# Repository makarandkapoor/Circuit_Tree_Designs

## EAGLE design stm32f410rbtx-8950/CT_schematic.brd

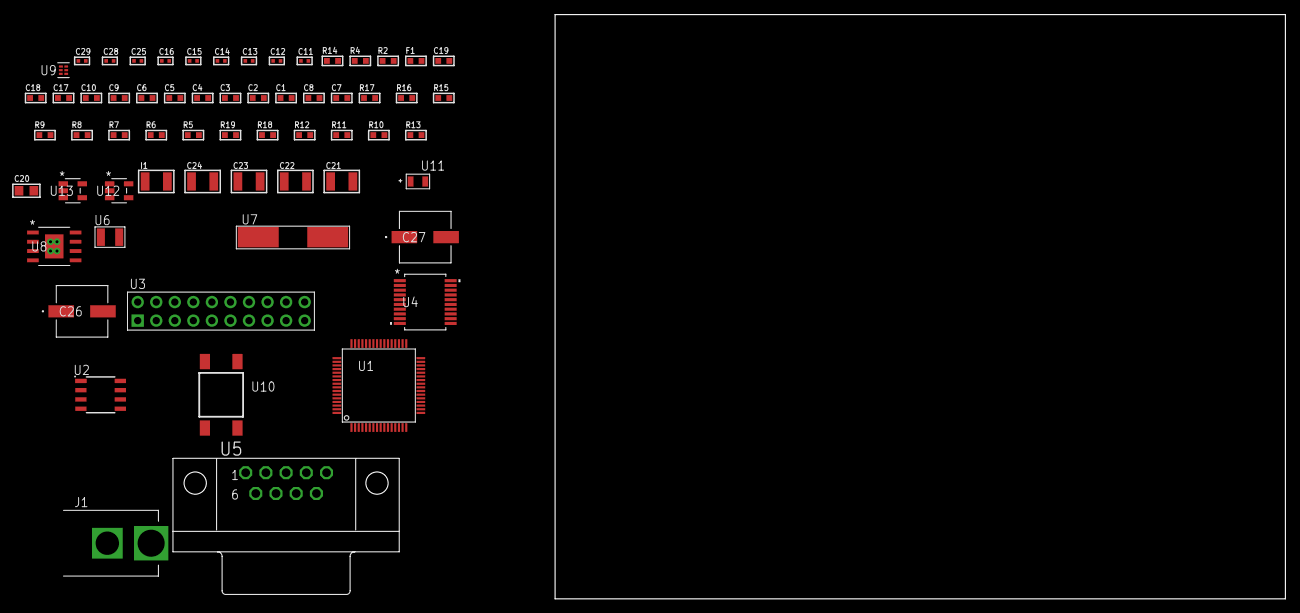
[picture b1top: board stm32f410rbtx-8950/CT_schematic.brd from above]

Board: 2 copper layers, 100.0 x 80.0 mm, 62 parts (0 on the bottom side), 43 nets, no tracks yet.

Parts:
C1, C10, C17, C18, C19: 1e-06; C0603
C2, C3, C4, C5, C6: 1e-07; C0603
C7: 4.7e-06; C0603
C8: 2.2e-06; C0603
C9: 1e-08; C0603
C11, C12, C13, C14: 1e-11; C0402
C15, C28, C29: 1e-08; C0402
C16, C25: 1e-07; C0402
C20: 4.7e-06; C0805
C21, C22, C23, C24: 1e-05; C1210
C26, C27: 0.0001; EXV-9H
F1: 240.0; L0603
I1: 1.5e-05; L1210
J1: PJ-037B; PJ-037B_PACKAGE
R2: 1000.0; R0603
R4: 4700.0; R0603
R5, R6, R7, R8, R9, R15, R16: 10000.0; R0603
R10, R11, R12: 100000.0; R0603
R13: 1402.2764227642; R0603
R14: 2200.0; R0603
R17: 82000.0; R0603
R18: 300000.0; R0603
R19: 120000.0; R0603
U1: STM32F410RBT6; LQFP64
U2: AT25128B-SSHL-T; SOIC-8
U3: TST-110-05-T-D-RA
U4: MAX3218EAP+T; SSOP-20
U5: 182-009-113R531; 182-009-MALE
U6: ABS07-32.768KHZ-7-T
U7: ABLS-25.000MHZ-B2F-T
U8: MIC5234YME; SOIC-8_EP
U9: TPS3895ADRYR; SON-6
U10: 4-1437565-2; SW_4-1437565-2
U11: Q65110A2395; LGM67K-G1J2-24-Z
U12, U13: nc7sz125m5x; NC7SZ125M5X

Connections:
CLK_CRYSTAL_U1_3: C11.1, U1.3, U6.1
CLK_CRYSTAL_U1_4: C12.1, U1.4, U6.2
CLK_CRYSTAL_U1_5: C13.1, U1.5, U7.1
CLK_CRYSTAL_U1_6: C14.1, U1.6, U7.2
GND: C1.2, C2.2, C3.2, C4.2, C5.2, C6.2, C7.2, C8.2, C9.2, C10.2, C11.2, C12.2, C13.2, C14.2, C15.2, C16.2, C17.2, C18.2, C19.2, C21.2, C22.2, C23.2, C24.2, C25.2, C26.2, C27.2, C28.2, C29.2, J1.2, R2.2, R5.2, R14.2, R17.2, R19.2, U1.12, U1.18, U1.31, U1.47, U1.63, U2.4, U3.4, U3.6, U3.8, U3.10, U3.12, U3.14, U3.16, U3.18, U3.20, U4.5, U4.17, U4.20, U5.5, U8.7, U8.EPAD, U9.2, U11.C, U12.2, U12.3, U13.1, U13.3
NET_U1_7: R4.1, U1.7, U13.4
NET_U1_13: C9.1, C10.1, F1.1, U1.13
NET_U1_30: C8.1, U1.30
NET_U1_60: R5.1, U1.60
NET_U1_62: U10.3, U10.4
NET_U2_3: R6.1, U2.3
NET_U2_7: R8.1, U2.7
NET_U4_1: I1.1, U4.1
NET_U4_2: R10.1, U4.2
NET_U4_3: R11.1, U4.3
NET_U4_4: R12.1, U4.4
NET_U4_15: C19.1, U4.15
NET_U4_16: C20.2, U4.16
NET_U4_18: C20.1, U4.18
NET_U4_19: C18.1, U4.19
NET_U5_2: U4.12, U5.2
NET_U5_3: U4.14, U5.3
NET_U5_7: U4.11, U5.7
NET_U5_8: U4.13, U5.8
NET_U8_4: R13.2, R14.1, U8.4
NET_U9_1: R16.1, R17.1, U9.1
NET_U9_3: R18.2, R19.1, U9.3
NET_U9_4: R15.1, U9.4, U12.4, U13.2
NET_U10_1: R2.1, U10.1, U10.2
PROC_SPI1_MISO: U1.22, U2.2
PROC_SPI1_MOSI: U1.23, U2.5
PROC_SPI1_NSS: R7.1, U1.20, U2.1
PROC_SPI1_SCK: U1.21, U2.6
PROC_SYS_JTCK_SWCLK: U1.49, U3.9
PROC_SYS_JTDO_SWO: U1.55, U3.13
PROC_SYS_JTMS_SWDIO: U1.46, U3.7
PROC_USART1_CTS: U1.44, U4.8
PROC_USART1_RTS: U1.45, U4.10
PROC_USART1_RX: U1.43, U4.9
PROC_USART1_TX: U1.42, U4.7
RST_OUT_U3_SRESET_B: R9.1, U3.15, U12.1
VCC_S1_9V9: C21.1, C22.1, C26.1, C27.1, J1.1, U8.5, U8.8
VCC_TIER1_1V8: C1.1, C2.1, C3.1, C4.1, C5.1, C6.1, C7.1, C15.1, C16.1, C17.1, C23.1, C24.1, C25.1, C28.1, C29.1, F1.2, I1.2, R4.2, R6.2, R7.2, R8.2, R9.2, R10.2, R11.2, R12.2, R13.1, R15.2, R16.2, R18.1, U1.1, U1.19, U1.32, U1.48, U1.64, U2.8, U3.1, U4.6, U8.1, U9.6, U12.5, U13.5

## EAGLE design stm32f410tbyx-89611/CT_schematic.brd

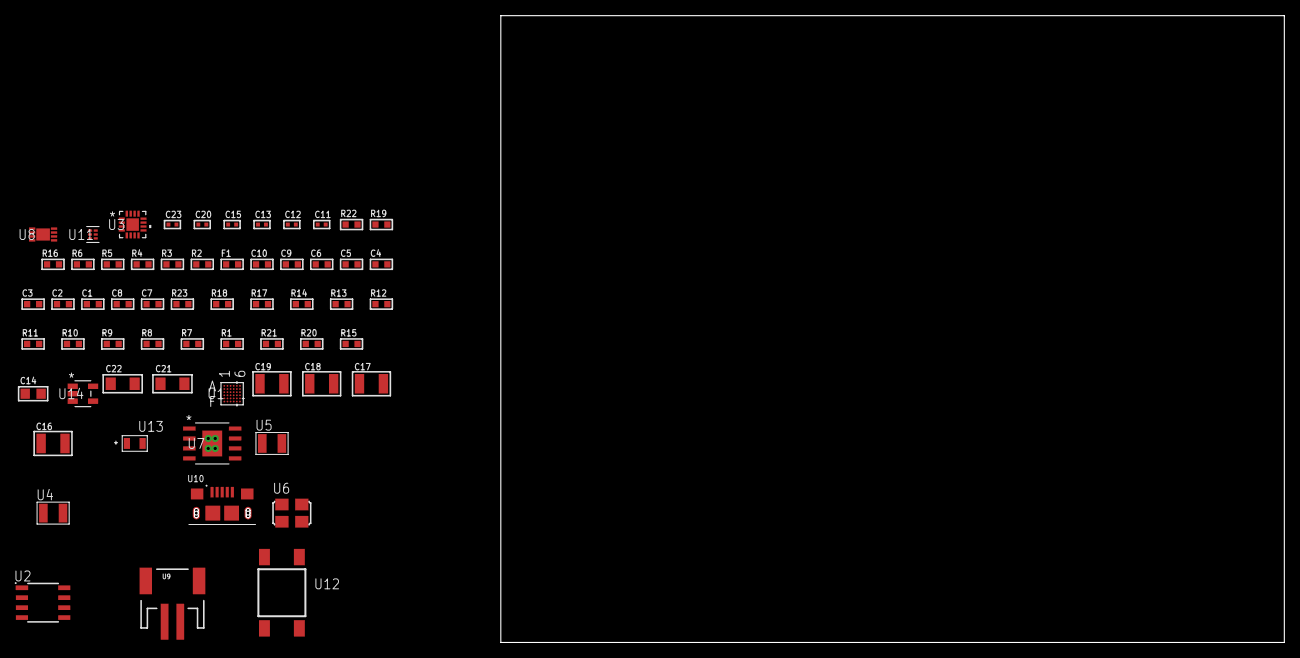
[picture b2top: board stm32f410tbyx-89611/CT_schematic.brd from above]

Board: 2 copper layers, 61 parts (0 on the bottom side), 33 nets, no tracks yet.

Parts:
C1, C10: 1e-06; C0603
C2, C3, C4, C5, C6: 1e-07; C0603
C7: 4.7e-06; C0603
C8: 2.2e-06; C0603
C9: 1e-08; C0603
C11, C12: 1e-11; C0402
C13, C15, C23: 1e-08; C0402
C14: 4.7e-06; C0805
C16, C17, C18, C19: 1e-05; C1210
C20: 1e-07; C0402
C21, C22: 1e-05; C1206
F1: 240.0; L0603
R1, R7, R8, R9, R10, R11, R12, R13, R14, R17, R18, R23: 10000.0; R0603
R2: 1000.0; R0603
R3: 1600.5; R0603
R4: 4700.0; R0603
R5, R6, R16: 2200.0; R0603
R15: 4031.5447154472; R0603
R19: 9100.0; R0603
R20: 680000.0; R0603
R21: 120000.0; R0603
R22: 2000.0; R0603
U1: STM32F410TBY6; WLCSP36
U2: AT25640B-SSHL-T; SOIC-8
U3: M41T65Q6F; M41T65_QFN-16
U4, U5: ABS07-32.768KHZ-7-T
U6: ASFL1-25MHZ-NCS; ASFL1
U7: MIC5234YME; SOIC-8_EP
U8: MCP73831T-2ACI/MC; DFN8_2X3MC
U9: S2B-PH-SM4-TB(LF)(SN); JST-2-SMD
U10: 10118193-0001LF; FCI_10118193-0001LF
U11: TPS3895ADRYR; SON-6
U12: 4-1437565-2; SW_4-1437565-2
U13: Q65110A2395; LGM67K-G1J2-24-Z
U14: nc7sz125m5x; NC7SZ125M5X

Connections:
CLK_CRYSTAL_U1_B6: C11.1, U1.B6, U5.1
CLK_CRYSTAL_U1_C6: C12.1, U1.C6, U5.2
CLK_CRYSTAL_U3_1: U3.1, U4.1
CLK_CRYSTAL_U3_2: U3.2, U4.2
CLK_U1_C5: U1.C5, U6.3
GND: C1.2, C2.2, C3.2, C4.2, C5.2, C6.2, C7.2, C8.2, C9.2, C10.2, C11.2, C12.2, C13.2, C14.2, C15.2, C16.2, C17.2, C18.2, C19.2, C20.2, C21.2, C22.2, C23.2, R2.2, R8.2, R16.2, R19.2, R21.2, R22.2, U1.A5, U1.B1, U1.E6, U1.F2, U2.4, U3.3, U3.5, U3.17, U6.2, U7.7, U7.EPAD, U8.6, U8.9, U9.2, U10.5, U10.6, U10.7, U10.8, U10.9, U11.2, U13.C, U14.1, U14.3
INPUT_USBPOWER_5V: C21.1, R23.2, U8.1, U8.2, U10.1
NET_U1_A4: R5.1, U1.A4, U3.10
NET_U1_B4: R7.1, R9.1, U1.B4
NET_U1_C3: R6.1, U1.C3, U3.9
NET_U1_D4: R8.1, U1.D4
NET_U1_D5: R4.1, U1.D5, U14.4
NET_U1_E2: C8.1, U1.E2
NET_U1_F4: R3.1, U1.F4, U13.A
NET_U1_F5: R1.1, U1.F5, U12.3, U12.4
NET_U1_F6: C9.1, C10.1, F1.1, U1.F6
NET_U2_3: R10.1, U2.3
NET_U2_7: R12.1, U2.7
NET_U3_4: R13.1, U3.4
NET_U3_11: R14.1, U3.11
NET_U7_4: R15.2, R16.1, U7.4
NET_U8_5: R23.1, U8.5
NET_U8_8: R22.1, U8.8
NET_U11_1: R18.1, R19.1, U11.1
NET_U11_3: R20.2, R21.1, U11.3
NET_U11_4: R17.1, U11.4, U14.2
NET_U12_1: R2.1, U12.1, U12.2
PROC_SPI1_MISO: U1.D3, U2.2
PROC_SPI1_MOSI: U1.A3, U2.5
PROC_SPI1_NSS: R11.1, U1.A2, U2.1
PROC_SPI1_SCK: U1.C2, U2.6
VCC_S1_3V7: C16.1, C17.1, C22.1, U7.5, U7.8, U8.3, U8.4, U9.1
VCC_TIER1_3V3: C1.1, C2.1, C3.1, C4.1, C5.1, C6.1, C7.1, C13.1, C14.1, C15.1, C18.1, C19.1, C20.1, C23.1, F1.2, R1.2, R3.2, R4.2, R5.2, R6.2, R7.2, R9.2, R10.2, R11.2, R12.2, R13.2, R14.2, R15.1, R17.2, R18.2, R20.1, U1.A1, U1.A6, U1.B5, U1.F1, U2.8, U3.14, U6.4, U7.1, U11.6, U14.5

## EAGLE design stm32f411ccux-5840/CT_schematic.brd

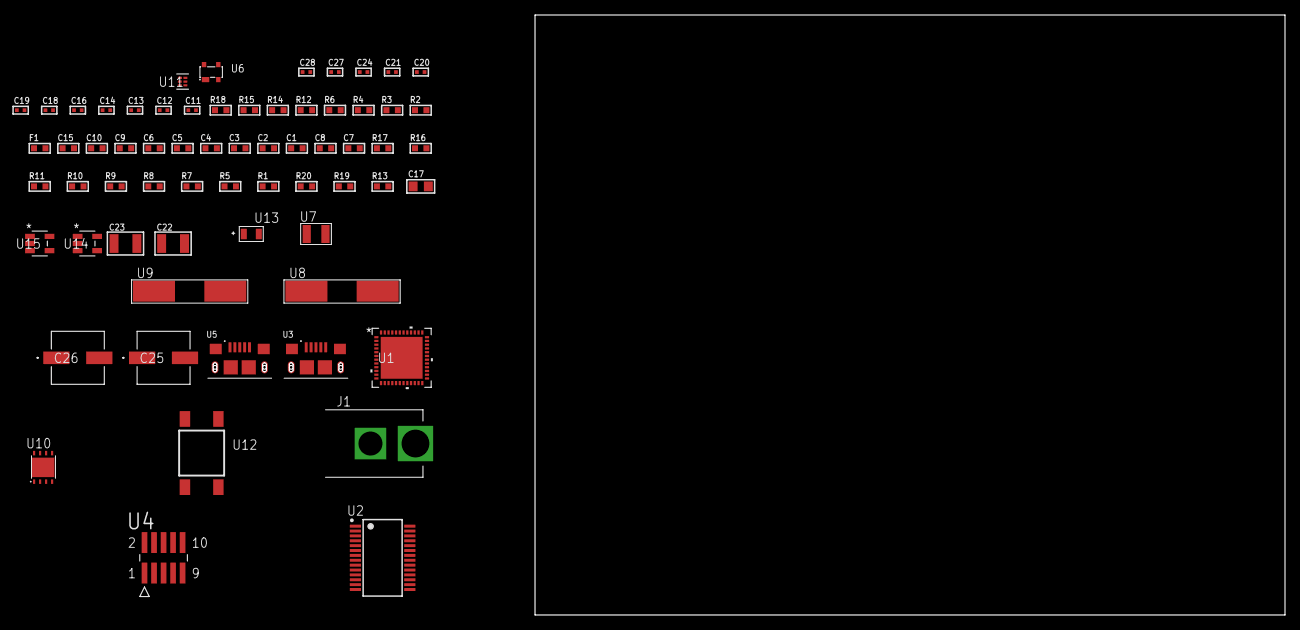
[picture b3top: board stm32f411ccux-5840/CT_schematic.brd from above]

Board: 2 copper layers, 65 parts (0 on the bottom side), 40 nets, no tracks yet.

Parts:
C1, C10, C15: 1e-06; C0603
C2, C3, C4, C5, C6: 1e-07; C0603
C7: 4.7e-06; C0603
C8: 2.2e-06; C0603
C9: 1e-08; C0603
C11, C12, C13, C14: 1e-11; C0402
C16, C18, C19, C20, C24: 1e-07; C0402
C17: 4.7e-06; C0805
C21, C27, C28: 1e-08; C0402
C22, C23: 1e-05; C1210
C25, C26: 0.0001; EXV-9H
F1: 240.0; L0603
J1: PJ-037B; PJ-037B_PACKAGE
R1, R5, R7, R8, R9, R10, R11, R16, R17: 10000.0; R0603
R2, R15: 1000.0; R0603
R3: 1600.5; R0603
R4, R6: 4700.0; R0603
R12: 5.0; R0603
R13: 100000.0; R0603
R14: 2231.0; R0603
R18: 9100.0; R0603
R19: 680000.0; R0603
R20: 120000.0; R0603
U1: STM32F411CCU6; UFQFPN48
U2: FT232RL-REEL; SSOP-28
U3, U5: 10118193-0001LF; FCI_10118193-0001LF
U4: FTSH-105-01-L-DV-K; SAMTEC_FTSH-105-01-L-DV-K
U6: prtr5v0u2ax; SOT143B
U7: ABS07-32.768KHZ-7-T
U8: ABLS-25.000MHZ-B2F-T
U9: ABLS-12.000MHZ-B4-T
U10: LP3878SDX-ADJ/NOPB; WSON-8
U11: TPS3895ADRYR; SON-6
U12: 4-1437565-2; SW_4-1437565-2
U13: Q65110A2395; LGM67K-G1J2-24-Z
U14, U15: nc7sz125m5x; NC7SZ125M5X

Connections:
CLK_CRYSTAL_U1_3: C11.1, U1.3, U7.1
CLK_CRYSTAL_U1_4: C12.1, U1.4, U7.2
CLK_CRYSTAL_U1_5: C13.1, U1.5, U8.1
CLK_CRYSTAL_U1_6: C14.1, U1.6, U8.2
CLK_CRYSTAL_U2_27: U2.27, U9.1
CLK_CRYSTAL_U2_28: U2.28, U9.2
GND: C1.2, C2.2, C3.2, C4.2, C5.2, C6.2, C7.2, C8.2, C9.2, C10.2, C11.2, C12.2, C13.2, C14.2, C15.2, C16.2, C17.2, C18.2, C19.2, C20.2, C21.2, C22.2, C23.2, C24.2, C25.2, C26.2, C27.2, C28.2, J1.2, R2.2, R5.2, R8.2, R12.2, R15.2, R18.2, R20.2, U1.8, U1.23, U1.35, U1.47, U1.49, U2.7, U2.18, U2.21, U2.25, U2.26, U3.5, U3.6, U3.7, U3.8, U3.9, U4.3, U4.5, U5.5, U5.6, U5.7, U5.8, U5.9, U6.1, U10.3, U10.PAD, U11.2, U13.C, U14.2, U14.3, U15.1, U15.3
NET_U1_7: R4.1, U1.7, U15.4
NET_U1_9: C9.1, C10.1, F1.1, U1.9
NET_U1_22: C8.1, U1.22
NET_U1_44: R5.1, U1.44
NET_U1_45: R3.1, U1.45, U13.A
NET_U1_46: R1.1, U1.46, U12.3, U12.4
NET_U2_14: R7.1, U2.14
NET_U2_17: C18.1, U2.17
NET_U2_19: R8.1, U2.19
NET_U3_1: R6.1, U3.1
NET_U3_2: U2.16, U3.2
NET_U3_3: U2.15, U3.3
NET_U4_9: R12.1, U4.9
NET_U10_1: C21.1, U10.1
NET_U10_6: R14.2, R15.1, U10.6
NET_U10_8: R13.1, U10.8
NET_U11_1: R17.1, R18.1, U11.1
NET_U11_3: R19.2, R20.1, U11.3
NET_U11_4: R16.1, U11.4, U14.4, U15.2
NET_U12_1: R2.1, U12.1, U12.2
PROC_SYS_JTCK_SWCLK: R10.1, U1.37, U4.4
PROC_SYS_JTDO_SWO: U1.39, U4.6
PROC_SYS_JTMS_SWDIO: R11.1, U1.34, U4.2
PROC_USART2_CTS: U1.10, U2.3
PROC_USART2_RTS: U1.11, U2.11
PROC_USART2_RX: U1.13, U2.1
PROC_USART2_TX: U1.12, U2.5
PROC_USB_OTG_FS_DM: U1.32, U5.2, U6.3
PROC_USB_OTG_FS_DP: U1.33, U5.3, U6.2
PROC_USB_OTG_FS_VBUS: C15.1, U1.30, U5.1, U6.4
RST_OUT_U4_JTAG_RST_B: R9.1, U4.10, U14.1
VCC_S1_13V7: C22.1, C25.1, C26.1, J1.1, R13.2, U10.4
VCC_TIER1_3V3: C1.1, C2.1, C3.1, C4.1, C5.1, C6.1, C7.1, C16.1, C17.1, C19.1, C20.1, C23.1, C24.1, C27.1, C28.1, F1.2, R1.2, R3.2, R4.2, R7.2, R9.2, R10.2, R11.2, R14.1, R16.2, R17.2, R19.1, U1.1, U1.24, U1.36, U1.48, U2.4, U2.20, U4.1, U10.5, U11.6, U14.5, U15.5

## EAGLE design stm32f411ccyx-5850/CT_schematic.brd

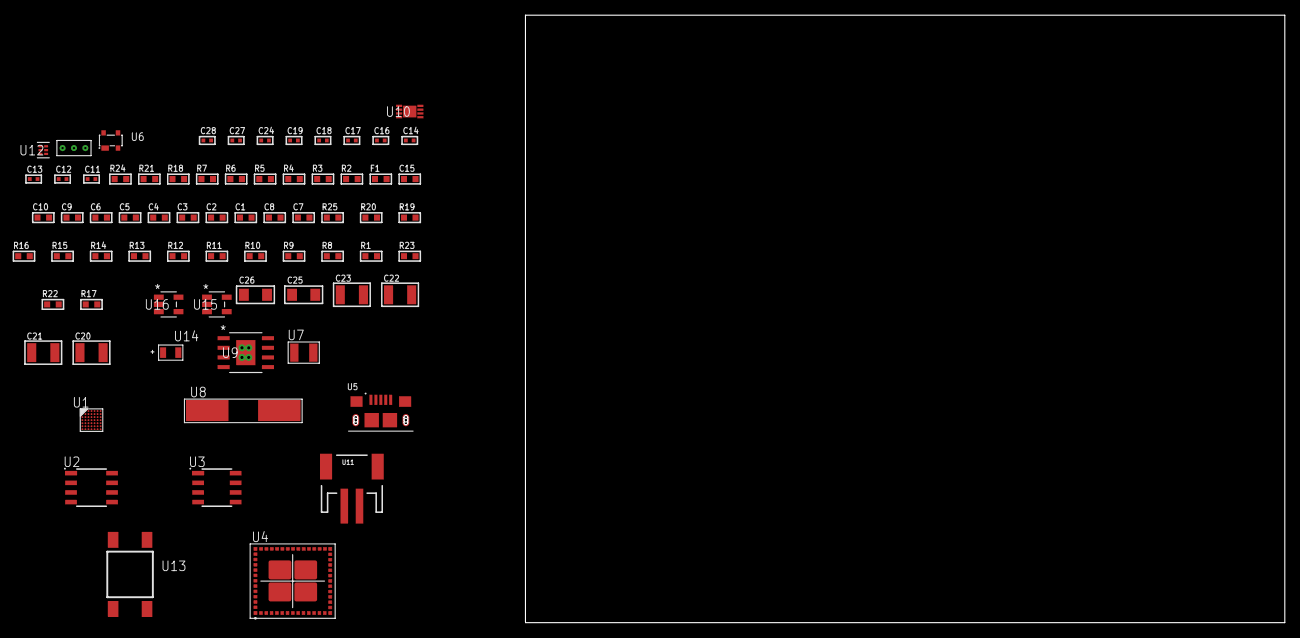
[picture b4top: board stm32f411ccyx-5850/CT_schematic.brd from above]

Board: 2 copper layers, 122.6 x 80.0 mm, 71 parts (0 on the bottom side), 43 nets, no tracks yet.

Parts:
C1, C10, C15: 1e-06; C0603
C2, C3, C4, C5, C6: 1e-07; C0603
C7: 4.7e-06; C0603
C8: 2.2e-06; C0603
C9: 1e-08; C0603
C11, C12, C13, C14: 1e-11; C0402
C16, C17, C27, C28: 1e-08; C0402
C18, C19, C24: 1e-07; C0402
C20, C21, C22, C23: 1e-05; C1210
C25, C26: 1e-05; C1206
F1: 240.0; L0603
R1, R8, R9, R10, R11, R12, R13, R14, R15, R16, R19, R20, R25: 10000.0; R0603
R2: 1000.0; R0603
R3: 1600.5; R0603
R4, R5: 4700.0; R0603
R6, R7, R18: 2200.0; R0603
R17: 4031.5447154472; R0603
R21: 9100.0; R0603
R22: 680000.0; R0603
R23: 120000.0; R0603
R24: 2000.0; R0603
U1: STM32F411CCY6; WLCSP49
U2: AT25040B-SSHL-T; SOIC-8
U3: AT24C02D-SSHM-T; AT24C02D
U4: MBH7BLZ02-109004
U5: 10118193-0001LF; FCI_10118193-0001LF
U6: prtr5v0u2ax; SOT143B
U7: ABS07-32.768KHZ-7-T
U8: ABLS-25.000MHZ-B2F-T
U9: MIC5234YME; SOIC-8_EP
U10: MCP73831T-2ACI/MC; DFN8_2X3MC
U11: S2B-PH-SM4-TB(LF)(SN); JST-2-SMD
U12: TPS3895ADRYR; SON-6
U13: 4-1437565-2; SW_4-1437565-2
U14: Q65110A2395; LGM67K-G1J2-24-Z
U15, U16: nc7sz125m5x; NC7SZ125M5X
U17: Dummy; DUMMY_PACKAGE_152

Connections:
CLK_CRYSTAL_U1_C6: C11.1, U1.C6, U7.1
CLK_CRYSTAL_U1_C7: C12.1, U1.C7, U7.2
CLK_CRYSTAL_U1_D6: C13.1, U1.D6, U8.1
CLK_CRYSTAL_U1_D7: C14.1, U1.D7, U8.2
GND: C1.2, C2.2, C3.2, C4.2, C5.2, C6.2, C7.2, C8.2, C9.2, C10.2, C11.2, C12.2, C13.2, C14.2, C15.2, C16.2, C17.2, C18.2, C19.2, C20.2, C21.2, C22.2, C23.2, C24.2, C25.2, C26.2, C27.2, C28.2, R2.2, R8.2, R13.2, R15.2, R16.2, R18.2, R21.2, R23.2, R24.2, U1.A6, U1.B1, U1.D3, U1.E6, U2.4, U3.4, U4.1, U4.3, U4.15, U4.27, U4.29, U4.41, U4.42, U4.43, U4.44, U4.45, U4.46, U4.47, U4.48, U4.49, U4.50, U4.52, U4.53, U4.54, U4.55, U4.56, U5.5, U5.6, U5.7, U5.8, U5.9, U6.1, U9.7, U9.EPAD, U10.6, U10.9, U11.2, U12.2, U14.C, U15.1, U15.3, U16.1, U16.3, U17.1
INPUT_USBPOWER_5V: C15.1, C25.1, R25.2, U1.D2, U5.1, U6.4, U10.1, U10.2
NET_U1_A5: R8.1, U1.A5
NET_U1_B5: R6.1, U1.B5, U3.6
NET_U1_B6: R9.1, U1.B6
NET_U1_C5: R7.1, U1.C5, U3.5
NET_U1_E7: R5.1, U1.E7, U16.4
NET_U1_F7: C9.1, C10.1, F1.1, U1.F7
NET_U1_G2: C8.1, U1.G2
NET_U1_G5: R3.1, U1.G5, U14.A
NET_U1_G6: R1.1, U1.G6, U13.3, U13.4
NET_U2_3: R10.1, U2.3
NET_U2_7: R12.1, U2.7
NET_U3_1: R14.1, U3.1
NET_U3_2: R15.1, U3.2
NET_U3_3: R16.1, U3.3
NET_U3_7: R13.1, U3.7
NET_U4_39: R4.1, U4.39, U15.4
NET_U9_4: R17.2, R18.1, U9.4
NET_U10_5: R25.1, U10.5
NET_U10_8: R24.1, U10.8
NET_U12_1: R20.1, R21.1, U12.1
NET_U12_3: R22.2, R23.1, U12.3
NET_U12_4: R19.1, U12.4, U15.2, U16.2
NET_U13_1: R2.1, U13.1, U13.2
PROC_ADC1_IN6: U1.F4, U17.2
PROC_ADC1_IN7: U1.F3, U17.3
PROC_SPI1_MISO: U1.A4, U2.2
PROC_SPI1_MOSI: U1.B4, U2.5
PROC_SPI1_NSS: R11.1, U1.A2, U2.1
PROC_SPI1_SCK: U1.A3, U2.6
PROC_USART2_CTS: U1.F6, U4.26
PROC_USART2_RTS: U1.G7, U4.24
PROC_USART2_RX: U1.E4, U4.25
PROC_USART2_TX: U1.E5, U4.23
PROC_USB_OTG_FS_DM: U1.C1, U5.2, U6.3
PROC_USB_OTG_FS_DP: U1.C3, U5.3, U6.2
VCC_S1_3V7: C20.1, C21.1, C26.1, U9.5, U9.8, U10.3, U10.4, U11.1
VCC_TIER1_3V3: C1.1, C2.1, C3.1, C4.1, C5.1, C6.1, C7.1, C16.1, C17.1, C18.1, C19.1, C22.1, C23.1, C24.1, C27.1, C28.1, F1.2, R1.2, R3.2, R4.2, R5.2, R6.2, R7.2, R9.2, R10.2, R11.2, R12.2, R14.2, R17.1, R19.2, R20.2, R22.1, U1.A7, U1.B2, U1.B7, U1.F2, U2.8, U3.8, U4.28, U9.1, U12.6, U15.5, U16.5

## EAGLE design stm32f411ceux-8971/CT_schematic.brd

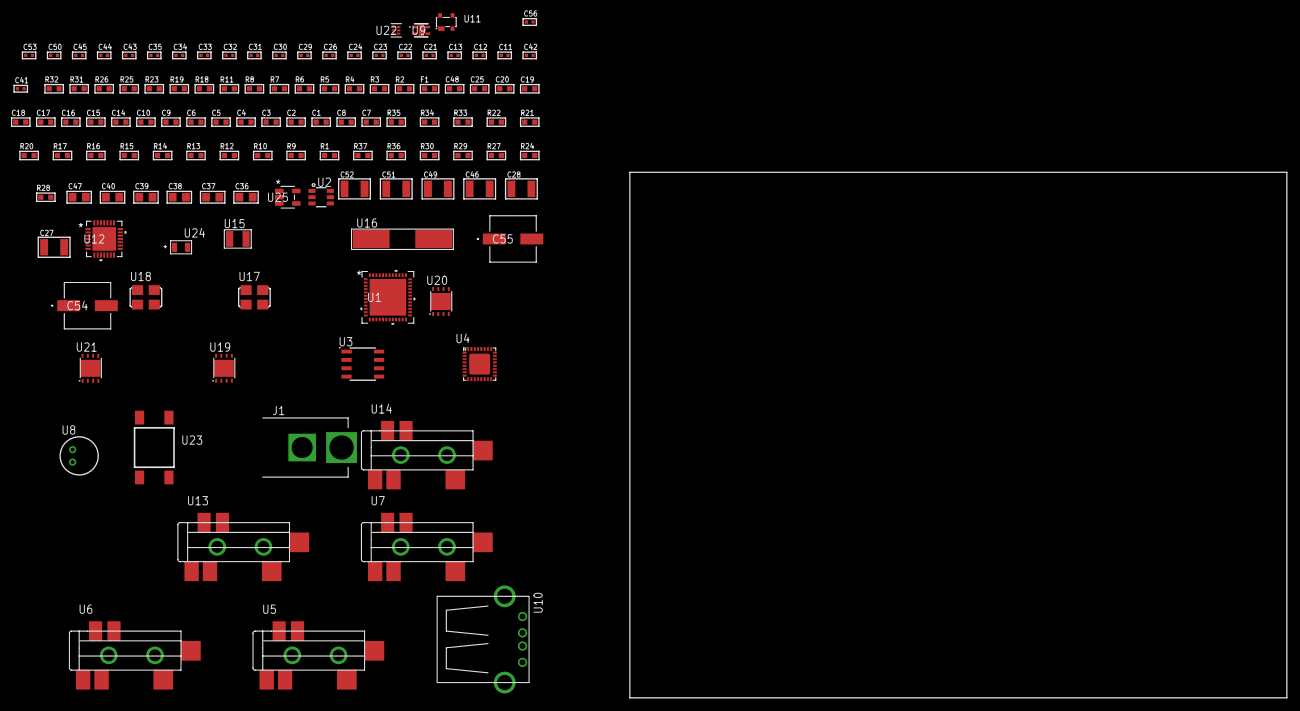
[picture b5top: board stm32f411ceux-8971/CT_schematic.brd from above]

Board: 2 copper layers, 100.0 x 80.0 mm, 120 parts (0 on the bottom side), 68 nets, no tracks yet.

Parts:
C1, C10, C14, C15, C16, C17, C18, C19, C20, C25: 1e-06; C0603
C2, C3, C4, C5, C6: 1e-07; C0603
C7: 4.7e-06; C0603
C8: 2.2e-06; C0603
C9: 1e-08; C0603
C11, C12: 1e-11; C0402
C13, C43, C44, C45, C50, C56: 1e-08; C0402
C21, C22, C23, C24, C26, C31, C32, C33, C34, C35, C53: 1e-07; C0402
C27, C28: 2.2e-05; C1210
C29, C30: 1e-09; C0402
C36, C37, C38, C39, C40, C47: 1e-05; C0805
C41, C42: 2.2e-11; C0402
C46, C49, C51, C52: 1e-05; C1210
C48: 8e-07; R0603
C54, C55: 0.0001; EXV-9H
F1: 240.0; L0603
J1: PJ-037B; PJ-037B_PACKAGE
R1, R10, R12, R13, R14, R15, R16, R17, R33, R34: 10000.0; R0603
R2, R26, R32: 1000.0; R0603
R3: 910.0; R0603
R4: 4700.0; R0603
R5, R6, R7, R8: 2200.0; R0603
R9, R20, R21, R22: 47000.0; R0603
R11, R18, R19: 1270.0; R0603
R23: 680.0; R0603
R24, R27, R29, R30: 100000.0; R0603
R25: 806.0; R0603
R28: 153694.38; R0603
R31: 3900.0; R0603
R35: 82000.0; R0603
R36: 300000.0; R0603
R37: 120000.0; R0603
U1: STM32F411CEU6; UFQFPN48
U2: MAX4995AAUT+T; SOT-23-6
U3: AT24C02D-SSHM-T; AT24C02D
U4: SGTL5000XNAA3; QFN-32
U5, U6, U7, U13, U14: SJ-43515TS-SMT-TR
U8: WM-64PCT; WM-64PC
U9: Si7034-A10-IM; SI7034-A10-IM
U10: 61400416021; USB-A-H
U11: prtr5v0u2ax; SOT143B
U12: WM8731CLSEFL; QFN-28
U15: ABS07-32.768KHZ-7-T
U16: ABLS-12.288MHZ-B4-T
U17: ASFL-24.57MHZ-NCS; ASFL1
U18: ASFL1-25MHZ-NCS; ASFL1
U19, U21: LP3878SDX-ADJ/NOPB; WSON-8
U20: LP2951ACSDX/NOPB; WSON-8
U22: TPS3895ADRYR; SON-6
U23: 4-1437565-2; SW_4-1437565-2
U24: Q65110A2395; LGM67K-G1J2-24-Z
U25: nc7sz125m5x; NC7SZ125M5X

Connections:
CLK_CRYSTAL_U1_3: C11.1, U1.3, U15.1
CLK_CRYSTAL_U1_4: C12.1, U1.4, U15.2
CLK_CRYSTAL_U12_1: C41.1, U12.1, U16.1
CLK_CRYSTAL_U12_2: C42.1, U12.2, U16.2
CLK_U1_5: U1.5, U18.3
CLK_U4_21: U4.21, U17.3
GND: C1.2, C2.2, C3.2, C4.2, C5.2, C6.2, C7.2, C8.2, C9.2, C10.2, C11.2, C12.2, C13.2, C21.2, C22.2, C23.2, C24.2, C25.2, C26.2, C30.2, C31.2, C32.2, C33.2, C34.2, C35.2, C36.2, C37.2, C38.2, C39.2, C40.2, C41.2, C42.2, C43.2, C44.2, C45.2, C46.2, C47.2, C48.2, C49.2, C50.2, C51.2, C52.2, C53.2, C54.2, C55.2, C56.2, J1.2, R2.2, R9.2, R10.2, R11.2, R13.2, R14.2, R16.2, R17.2, R19.2, R20.2, R21.2, R22.2, R26.2, R29.2, R32.2, R35.2, R37.2, U1.8, U1.23, U1.35, U1.47, U1.49, U2.2, U3.4, U4.1, U4.3, U4.7, U4.EXP, U6.1, U7.1, U8.2, U9.5, U10.4, U10.5, U10.6, U11.1, U12.4, U12.15, U12.19, U12.25, U12.26, U12.29, U13.1, U14.1, U17.2, U18.2, U19.3, U19.PAD, U20.3, U20.4, U20.PAD, U21.3, U21.PAD, U22.2, U24.C, U25.1, U25.3
NET_U1_7: R4.1, U1.7, U25.4
NET_U1_9: C9.1, C10.1, F1.1, U1.9
NET_U1_21: R7.1, U1.21, U3.6
NET_U1_22: C8.1, U1.22
NET_U1_31: R11.1, U1.31
NET_U1_39: R8.1, U1.39, U3.5
NET_U1_42: R5.1, U1.42, U9.2
NET_U1_43: R6.1, U1.43, U9.4
NET_U1_44: R10.1, U1.44
NET_U1_45: R3.1, U1.45, U24.A
NET_U1_46: R1.1, U1.46, U23.3, U23.4
NET_U2_3: R9.1, U2.3
NET_U3_1: R15.1, U3.1
NET_U3_2: R16.1, U3.2
NET_U3_3: R17.1, U3.3
NET_U3_7: R14.1, U3.7
NET_U4_10: C24.1, U4.10
NET_U4_29: R18.1, U4.29
NET_U4_31: R19.1, U4.31
NET_U5_1: U4.4, U5.1
NET_U5_2: U4.2, U5.2
NET_U5_5: U4.6, U5.5
NET_U6_2: C15.1, U6.2
NET_U6_5: C14.1, U6.5
NET_U7_2: C17.1, C18.1, U7.2
NET_U7_5: C16.1, U7.5
NET_U7_13: C17.2, C18.2
NET_U8_1: C19.1, C20.1, C25.1, U4.16, U8.1
NET_U8_15: C19.2, C20.2
NET_U12_20: C35.1, C40.1, U12.20
NET_U13_2: C28.1, R21.1, U13.2
NET_U13_5: C27.1, R20.1, U13.5
NET_U14_5: C29.1, C30.1, R22.1, R23.1, U14.5
NET_U19_1: C45.1, U19.1
NET_U19_6: R25.2, R26.1, U19.6
NET_U19_8: R24.1, U19.8
NET_U20_5: R27.1, U20.5
NET_U20_7: R28.2, R29.1, U20.7
NET_U21_1: C50.1, U21.1
NET_U21_6: R31.2, R32.1, U21.6
NET_U21_8: R30.1, U21.8
NET_U22_1: R34.1, R35.1, U22.1
NET_U22_3: R36.2, R37.1, U22.3
NET_U22_4: R33.1, U22.4, U25.2
NET_U23_1: R2.1, U23.1, U23.2
PROC_GPIO_TO_U1_USB_FAULT: R12.1, U1.6, U2.6
PROC_GPIO_TO_U1_VBUS_EN: R13.1, U1.2, U2.4
PROC_I2S1_CK: U1.15, U4.24
PROC_I2S1_SD: U1.17, U4.26
PROC_I2S1_WS: U1.14, U4.23
PROC_I2S2_CK: U1.26, U12.7
PROC_I2S2_EXT_SD: U1.27, U12.10
PROC_I2S2_SD: U1.28, U12.8
PROC_I2S2_WS: U1.25, U12.9, U12.11
PROC_USB_OTG_FS_DM: U1.32, U10.2, U11.3
PROC_USB_OTG_FS_DP: U1.33, U10.3, U11.2
PROC_USB_OTG_FS_VBUS: U1.30, U2.1, U10.1, U11.4
VCC_S1_11V5: C46.1, C48.1, C51.1, C54.1, C55.1, J1.1, R24.2, R30.2, U19.4, U20.8, U21.4
VCC_TIER1_1V8: C1.1, C2.1, C3.1, C4.1, C5.1, C6.1, C7.1, C13.1, C21.1, C22.1, C23.1, C26.1, C31.1, C32.1, C33.1, C34.1, C36.1, C37.1, C38.1, C39.1, C47.1, C53.1, C56.1, F1.2, R1.2, R3.2, R4.2, R5.2, R6.2, R7.2, R8.2, R12.2, R15.2, R18.2, R25.1, R33.2, R34.2, R36.1, U1.1, U1.24, U1.36, U1.48, U3.8, U4.5, U4.20, U4.30, U9.1, U12.3, U12.5, U12.12, U12.18, U19.5, U22.6, U25.5
VCC_TIER1_3V3: C43.1, C44.1, C49.1, R27.2, R28.1, U17.4, U18.4, U20.1
VCC_TIER1_5V0: C52.1, R31.1, U2.5, U21.5

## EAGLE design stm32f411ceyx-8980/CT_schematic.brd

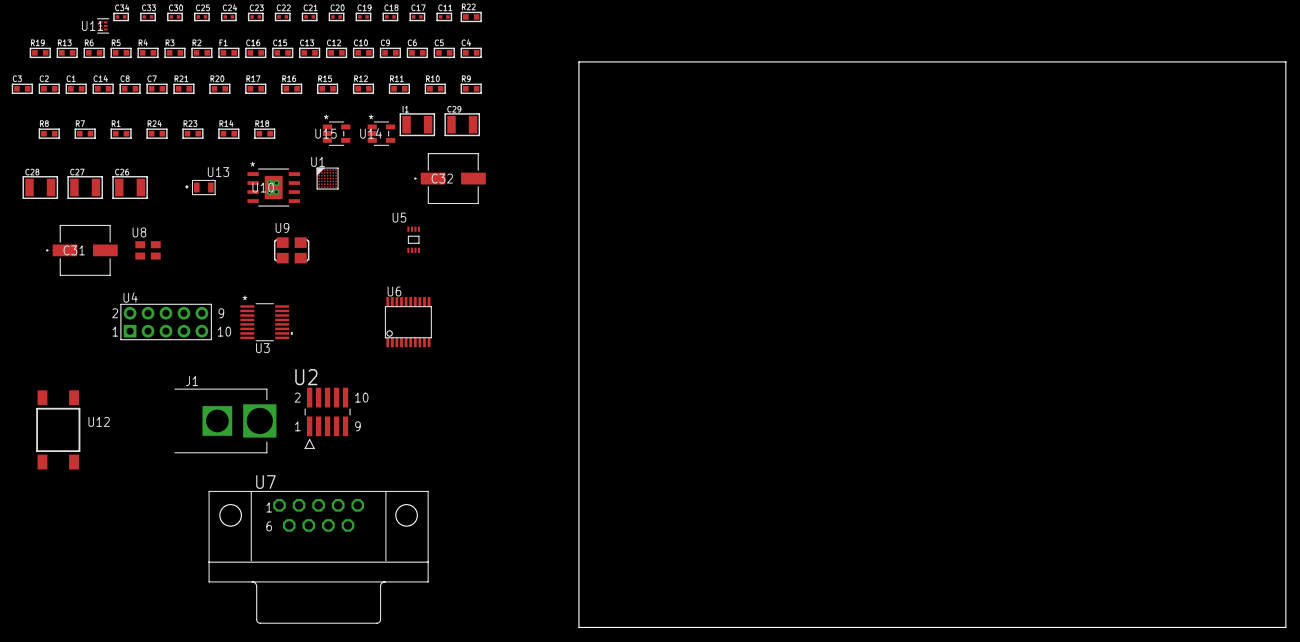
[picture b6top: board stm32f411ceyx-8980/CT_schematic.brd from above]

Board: 2 copper layers, 100.0 x 80.0 mm, 76 parts (0 on the bottom side), 55 nets, no tracks yet.

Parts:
C1, C10, C12, C13, C15, C16: 1e-06; C0603
C2, C3, C4, C5, C6: 1e-07; C0603
C7: 4.7e-06; C0603
C8: 2.2e-06; C0603
C9: 1e-08; C0603
C11, C18, C19, C20, C21, C22, C23, C30: 1e-07; C0402
C14: 2.2e-07; C0603
C17, C24, C25, C33, C34: 1e-08; C0402
C26, C27, C28, C29: 1e-05; C1210
C31, C32: 0.0001; EXV-9H
F1: 240.0; L0603
I1: 1e-05; L1210
J1: PJ-037B; PJ-037B_PACKAGE
R1, R7, R8, R9, R10, R11, R12, R15, R16, R17, R20, R21: 10000.0; R0603
R2: 1000.0; R0603
R3: 1600.5; R0603
R4: 4700.0; R0603
R5, R6, R19: 2200.0; R0603
R13: 5.0; R0603
R14: 100000.0; R0603
R18: 4031.5447154472; R0603
R22: 9100.0; R0603
R23: 680000.0; R0603
R24: 120000.0; R0603
U1: STM32F411CEY3; WLCSP49
U2: FTSH-105-01-L-DV-K; SAMTEC_FTSH-105-01-L-DV-K
U3: LTC2804CGN-1#PBF; SSOP-16
U4: HTSS-105-01-G-D
U5: 24AA64T-I/MNY; TDFN-8/6MM
U6: SP3203ECY-L/TR; TSSOP20-I
U7: 182-009-113R531; 182-009-MALE
U8: ASEK-32.768KHz-ECST; ASEK
U9: ASFL1-25MHZ-NCS; ASFL1
U10: MIC5234YME; SOIC-8_EP
U11: TPS3895ADRYR; SON-6
U12: 4-1437565-2; SW_4-1437565-2
U13: Q65110A2395; LGM67K-G1J2-24-Z
U14, U15: nc7sz125m5x; NC7SZ125M5X

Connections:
CLK_U1_C7: U1.C7, U8.3
CLK_U1_D7: U1.D7, U9.3
GND: C1.2, C2.2, C3.2, C4.2, C5.2, C6.2, C7.2, C8.2, C9.2, C10.2, C11.2, C12.2, C13.2, C15.2, C16.2, C17.2, C18.2, C19.2, C22.2, C23.2, C24.2, C25.2, C26.2, C27.2, C28.2, C29.2, C30.2, C31.2, C32.2, C33.2, C34.2, J1.2, R2.2, R7.2, R12.2, R13.2, R17.2, R19.2, R22.2, R24.2, U1.A6, U1.B1, U1.D3, U1.E6, U2.3, U2.5, U3.8, U4.9, U5.4, U6.18, U7.5, U8.2, U9.2, U10.7, U10.EPAD, U11.2, U13.C, U14.2, U14.3, U15.1, U15.3
NET_U1_A5: R7.1, U1.A5
NET_U1_B5: R5.1, U1.B5, U5.6
NET_U1_B6: R8.1, U1.B6
NET_U1_C5: R6.1, U1.C5, U5.5
NET_U1_E7: R4.1, U1.E7, U15.4
NET_U1_F7: C9.1, C10.1, F1.1, U1.F7
NET_U1_G2: C8.1, U1.G2
NET_U1_G5: R3.1, U1.G5, U13.A
NET_U1_G6: R1.1, U1.G6, U12.3, U12.4
NET_U2_9: R13.1, U2.9
NET_U3_6: C12.1, U3.6
NET_U3_7: C14.1, I1.2, U3.7
NET_U3_9: C13.1, U3.9
NET_U3_10: C14.2, U3.10
NET_U3_11: R14.1, U3.11
NET_U4_3: U3.1, U4.3
NET_U4_4: U3.2, U4.4
NET_U4_5: U3.3, U4.5
NET_U4_6: U3.4, U4.6
NET_U5_1: R15.1, U5.1
NET_U5_2: R16.1, U5.2
NET_U5_3: R17.1, U5.3
NET_U6_1: C20.1, U6.1
NET_U6_2: C22.1, U6.2
NET_U6_3: C20.2, U6.3
NET_U6_4: C21.1, U6.4
NET_U6_5: C21.2, U6.5
NET_U6_6: C23.1, U6.6
NET_U7_2: U6.14, U7.2
NET_U7_3: U6.17, U7.3
NET_U7_7: U6.13, U7.7
NET_U7_8: U6.16, U7.8
NET_U10_4: R18.2, R19.1, U10.4
NET_U11_1: R21.1, R22.1, U11.1
NET_U11_3: R23.2, R24.1, U11.3
NET_U11_4: R20.1, U11.4, U14.4, U15.2
NET_U12_1: R2.1, U12.1, U12.2
PROC_SYS_JTCK_SWCLK: R12.1, U1.A1, U2.4
PROC_SYS_JTDI: R10.1, U1.A2, U2.8
PROC_SYS_JTDO_SWO: U1.A3, U2.6
PROC_SYS_JTMS_SWDIO: R11.1, U1.B3, U2.2
PROC_USART1_CTS: U1.C1, U6.8
PROC_USART1_RTS: U1.C3, U6.10
PROC_USART1_RX: U1.C2, U6.11
PROC_USART1_TX: U1.C4, U6.7
PROC_USART2_CTS: U1.F6, U3.13
PROC_USART2_RTS: U1.G7, U3.15
PROC_USART2_RX: U1.E4, U3.16
PROC_USART2_TX: U1.E5, U3.14
RST_OUT_U2_JTAG_RST_B: R9.1, U2.10, U14.1
VCC_S1_6V7: C26.1, C27.1, C31.1, C32.1, J1.1, U10.5, U10.8
VCC_TIER1_3V3: C1.1, C2.1, C3.1, C4.1, C5.1, C6.1, C7.1, C11.1, C15.1, C16.1, C17.1, C18.1, C19.1, C24.1, C25.1, C28.1, C29.1, C30.1, C33.1, C34.1, F1.2, I1.1, R1.2, R3.2, R4.2, R5.2, R6.2, R8.2, R9.2, R10.2, R11.2, R14.2, R15.2, R16.2, R18.1, R20.2, R21.2, R23.1, U1.A7, U1.B2, U1.B7, U1.F2, U2.1, U3.5, U3.12, U5.7, U5.8, U6.12, U6.19, U8.4, U9.4, U10.1, U11.6, U14.5, U15.5

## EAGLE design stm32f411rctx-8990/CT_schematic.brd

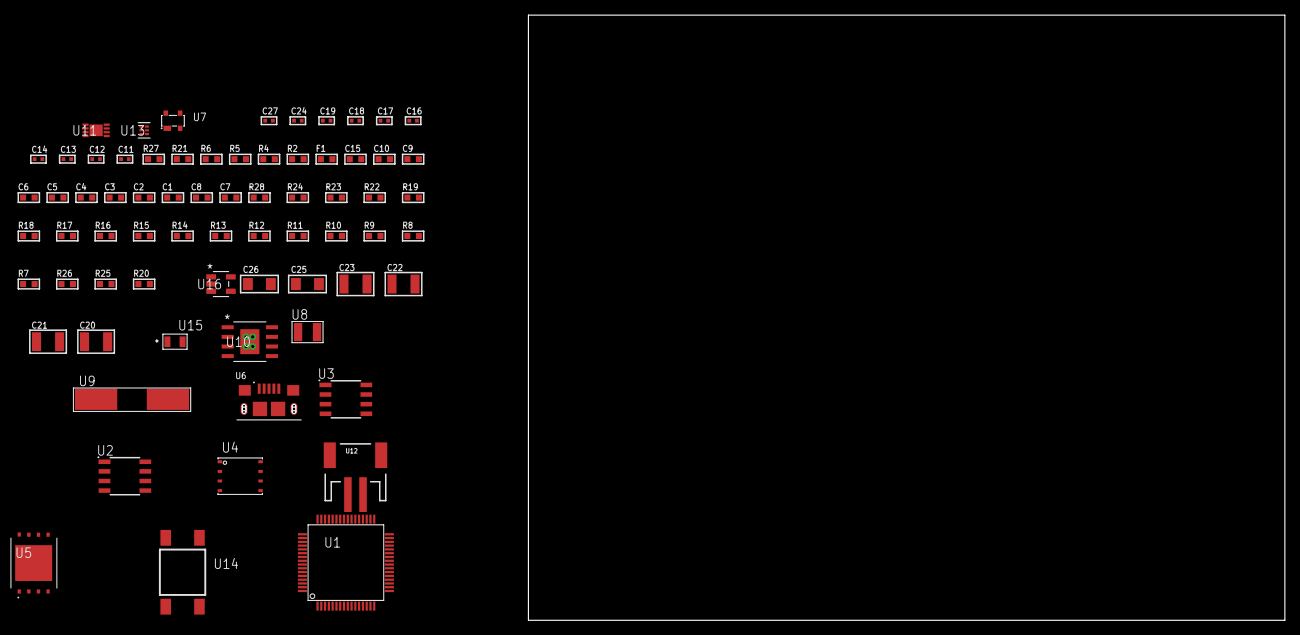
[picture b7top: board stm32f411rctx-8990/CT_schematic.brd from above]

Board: 2 copper layers, 70 parts (0 on the bottom side), 45 nets, no tracks yet.

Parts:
C1, C10, C15: 1e-06; C0603
C2, C3, C4, C5, C6: 1e-07; C0603
C7: 4.7e-06; C0603
C8: 2.2e-06; C0603
C9: 1e-08; C0603
C11, C12, C13, C14: 1e-11; C0402
C16, C17, C18, C19, C27: 1e-08; C0402
C20, C21, C22, C23: 1e-05; C1210
C24: 1e-07; C0402
C25, C26: 1e-05; C1206
F1: 240.0; L0603
R2: 1000.0; R0603
R4: 4700.0; R0603
R5, R6, R21: 2200.0; R0603
R7, R8, R9, R10, R11, R12, R13, R14, R15, R16, R17, R18, R19, R22, R23, R28: 10000.0; R0603
R20: 1402.2764227642; R0603
R24: 82000.0; R0603
R25: 300000.0; R0603
R26: 120000.0; R0603
R27: 2000.0; R0603
U1: STM32F411RCT7; LQFP64
U2: AT25640B-SSHL-T; SOIC-8
U3: AT25M02-SSHD-T; SOIC-8
U4: 24AA512-I/MF; DFN8-S
U5: S25FL128SDPNFI001; WNG008
U6: 10118193-0001LF; FCI_10118193-0001LF
U7: prtr5v0u2ax; SOT143B
U8: ABS07-32.768KHZ-7-T
U9: ABLS-25.000MHZ-B2F-T
U10: MIC5234YME; SOIC-8_EP
U11: MCP73831T-2ACI/MC; DFN8_2X3MC
U12: S2B-PH-SM4-TB(LF)(SN); JST-2-SMD
U13: TPS3895ADRYR; SON-6
U14: 4-1437565-2; SW_4-1437565-2
U15: Q65110A2395; LGM67K-G1J2-24-Z
U16: nc7sz125m5x; NC7SZ125M5X

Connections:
CLK_CRYSTAL_U1_3: C11.1, U1.3, U8.1
CLK_CRYSTAL_U1_4: C12.1, U1.4, U8.2
CLK_CRYSTAL_U1_5: C13.1, U1.5, U9.1
CLK_CRYSTAL_U1_6: C14.1, U1.6, U9.2
GND: C1.2, C2.2, C3.2, C4.2, C5.2, C6.2, C7.2, C8.2, C9.2, C10.2, C11.2, C12.2, C13.2, C14.2, C15.2, C16.2, C17.2, C18.2, C19.2, C20.2, C21.2, C22.2, C23.2, C24.2, C25.2, C26.2, C27.2, R2.2, R7.2, R16.2, R21.2, R24.2, R26.2, R27.2, U1.12, U1.18, U1.31, U1.44, U1.47, U1.63, U2.4, U3.4, U4.4, U5.4, U5.PAD, U6.5, U6.6, U6.7, U6.8, U6.9, U7.1, U10.7, U10.EPAD, U11.6, U11.9, U12.2, U13.2, U15.C, U16.1, U16.3
INPUT_USBPOWER_5V: C15.1, C25.1, R28.2, U1.42, U6.1, U7.4, U11.1, U11.2
NET_U1_7: R4.1, U1.7, U16.4
NET_U1_13: C9.1, C10.1, F1.1, U1.13
NET_U1_30: C8.1, U1.30
NET_U1_58: R5.1, U1.58, U4.6
NET_U1_59: R6.1, U1.59, U4.5
NET_U1_60: R7.1, U1.60
NET_U1_62: U14.3, U14.4
NET_U2_3: R8.1, U2.3
NET_U2_7: R10.1, U2.7
NET_U3_3: R11.1, U3.3
NET_U3_7: R13.1, U3.7
NET_U4_1: R14.1, U4.1
NET_U4_2: R15.1, U4.2
NET_U4_3: R16.1, U4.3
NET_U5_3: R17.1, U5.3
NET_U5_7: R19.1, U5.7
NET_U10_4: R20.2, R21.1, U10.4
NET_U11_5: R28.1, U11.5
NET_U11_8: R27.1, U11.8
NET_U13_1: R23.1, R24.1, U13.1
NET_U13_3: R25.2, R26.1, U13.3
NET_U13_4: R22.1, U13.4, U16.2
NET_U14_1: R2.1, U14.1, U14.2
PROC_SPI1_MISO: U1.22, U3.2
PROC_SPI1_MOSI: U1.23, U3.5
PROC_SPI1_NSS: R12.1, U1.20, U3.1
PROC_SPI1_SCK: U1.21, U3.6
PROC_SPI2_MISO: U1.10, U2.2
PROC_SPI2_MOSI: U1.11, U2.5
PROC_SPI2_NSS: R9.1, U1.33, U2.1
PROC_SPI2_SCK: U1.29, U2.6
PROC_SPI3_MISO: U1.52, U5.2
PROC_SPI3_MOSI: U1.53, U5.5
PROC_SPI3_NSS: R18.1, U1.50, U5.1
PROC_SPI3_SCK: U1.51, U5.6
PROC_USB_OTG_FS_DM: U1.44, U6.2, U7.3
PROC_USB_OTG_FS_DP: U1.45, U6.3, U7.2
VCC_S1_3V7: C20.1, C21.1, C26.1, U10.5, U10.8, U11.3, U11.4, U12.1
VCC_TIER1_1V8: C1.1, C2.1, C3.1, C4.1, C5.1, C6.1, C7.1, C16.1, C17.1, C18.1, C19.1, C22.1, C23.1, C24.1, C27.1, F1.2, R4.2, R5.2, R6.2, R8.2, R9.2, R10.2, R11.2, R12.2, R13.2, R14.2, R15.2, R17.2, R18.2, R19.2, R20.1, R22.2, R23.2, R25.1, U1.1, U1.19, U1.32, U1.48, U1.64, U2.8, U3.8, U4.7, U4.8, U5.8, U10.1, U13.6, U16.5

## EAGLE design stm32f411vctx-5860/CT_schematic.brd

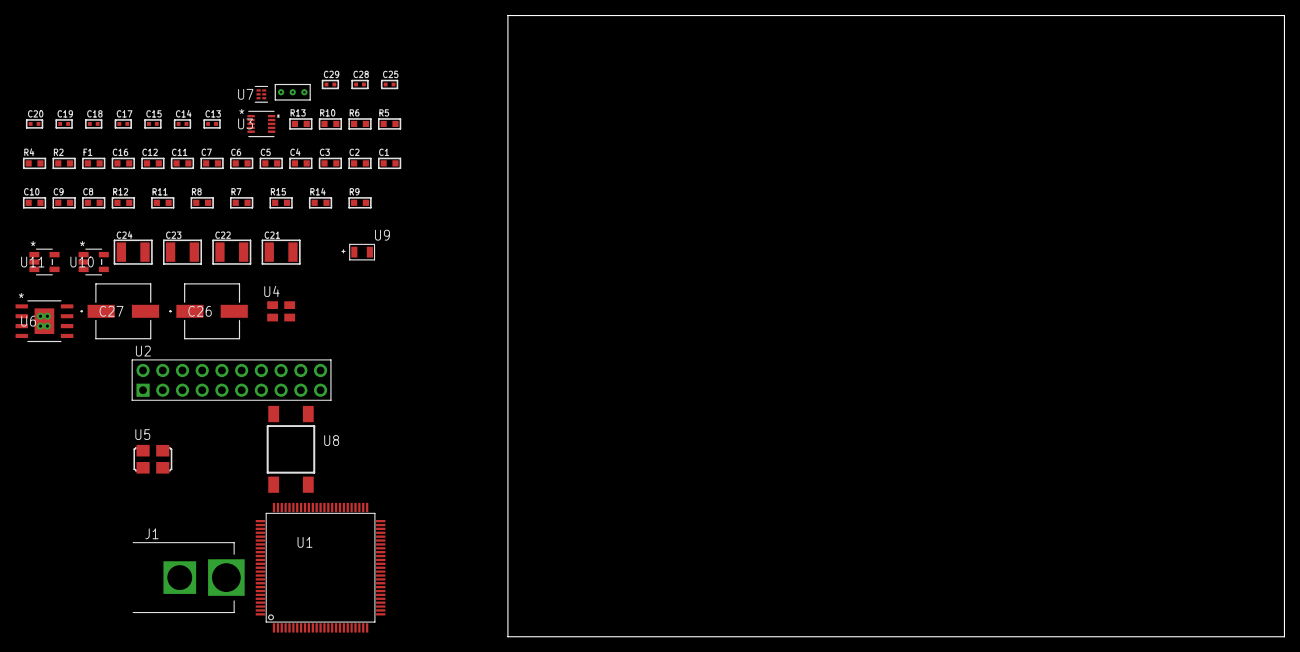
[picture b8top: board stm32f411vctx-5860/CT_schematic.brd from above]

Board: 2 copper layers, 100.0 x 80.0 mm, 56 parts (0 on the bottom side), 26 nets, no tracks yet.

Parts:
C1, C12, C16: 1e-06; C0603
C2, C3, C4, C5, C6, C7: 1e-07; C0603
C8: 4.7e-06; C0603
C9, C10: 2.2e-06; C0603
C11: 1e-08; C0603
C13, C14, C15, C17, C18, C25: 1e-07; C0402
C19, C20, C28, C29: 1e-08; C0402
C21, C22, C23, C24: 1e-05; C1210
C26, C27: 0.0001; EXV-9H
F1: 240.0; L0603
J1: PJ-037B; PJ-037B_PACKAGE
R2: 1000.0; R0603
R4: 4700.0; R0603
R5, R6, R10: 2200.0; R0603
R7, R8, R11, R12: 10000.0; R0603
R9: 4031.5447154472; R0603
R13: 9100.0; R0603
R14: 680000.0; R0603
R15: 120000.0; R0603
U1: STM32F411VCT6; LQFP100
U2: TST-110-05-T-D-RA
U3: MAG3110FCR1; DFN-10
U4: ASEK-32.768KHz-ECST; ASEK
U5: ASFL1-25MHZ-NCS; ASFL1
U6: MIC5234YME; SOIC-8_EP
U7: TPS3895ADRYR; SON-6
U8: 4-1437565-2; SW_4-1437565-2
U9: Q65110A2395; LGM67K-G1J2-24-Z
U10, U11: nc7sz125m5x; NC7SZ125M5X
U12: Dummy; DUMMY_PACKAGE_121

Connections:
CLK_U1_8: U1.8, U4.3
CLK_U1_12: U1.12, U5.3
GND: C1.2, C2.2, C3.2, C4.2, C5.2, C6.2, C7.2, C8.2, C9.2, C10.2, C11.2, C12.2, C13.2, C14.2, C15.2, C16.2, C17.2, C18.2, C19.2, C20.2, C21.2, C22.2, C23.2, C24.2, C25.2, C26.2, C27.2, C28.2, C29.2, J1.2, R2.2, R7.2, R10.2, R13.2, R15.2, U1.10, U1.20, U1.27, U1.49, U1.74, U1.99, U2.4, U2.6, U2.8, U2.10, U2.12, U2.14, U2.16, U2.18, U2.20, U3.5, U3.10, U4.2, U5.2, U6.7, U6.EPAD, U7.2, U9.C, U10.2, U10.3, U11.1, U11.3, U12.1
NET_U1_14: R4.1, U1.14, U11.4
NET_U1_22: C11.1, C12.1, F1.1, U1.21, U1.22
NET_U1_48: C9.1, U1.48
NET_U1_73: C10.1, U1.73
NET_U1_92: R5.1, U1.92, U3.7
NET_U1_93: R6.1, U1.93, U3.6
NET_U1_94: R7.1, U1.94
NET_U1_98: U8.3, U8.4
NET_U3_1: C14.1, U3.1
NET_U3_4: C17.1, U3.4
NET_U6_4: R9.2, R10.1, U6.4
NET_U7_1: R12.1, R13.1, U7.1
NET_U7_3: R14.2, R15.1, U7.3
NET_U7_4: R11.1, U7.4, U10.4, U11.2
NET_U8_1: R2.1, U8.1, U8.2
PROC_ADC1_IN1: U1.24, U12.3
PROC_ADC1_IN2: U1.25, U12.2
PROC_SYS_JTCK_SWCLK: U1.76, U2.9
PROC_SYS_JTDO_SWO: U1.89, U2.13
PROC_SYS_JTMS_SWDIO: U1.72, U2.7
RST_OUT_U2_SRESET_B: R8.1, U2.15, U10.1
VCC_S1_12V8: C21.1, C22.1, C26.1, C27.1, J1.1, U6.5, U6.8
VCC_TIER1_3V3: C1.1, C2.1, C3.1, C4.1, C5.1, C6.1, C7.1, C8.1, C13.1, C15.1, C16.1, C18.1, C19.1, C20.1, C23.1, C24.1, C25.1, C28.1, C29.1, F1.2, R4.2, R5.2, R6.2, R8.2, R9.1, R11.2, R12.2, R14.1, U1.6, U1.11, U1.19, U1.28, U1.50, U1.75, U1.100, U2.1, U3.2, U3.8, U4.4, U5.4, U6.1, U7.6, U10.5, U11.5
